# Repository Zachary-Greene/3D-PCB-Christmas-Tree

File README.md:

# 3D-PCB-Christmas-Tree
This is a repository for my 3D free standing PCB christmas tree project. It is two PCB's that slide together to create a free standing decoration. To secure the PCB's together, you solder them together using the exposed pads that ideally will line up. Included within the repository is a copy of this readme file, a license file and the eagle files.

## Parts and Assembly
### Assembly
Solder the smallest components on the boards first otherwise it'll be harder if you solder the bigger parts first. Then solder the larger components such as the battery holder. Afterwards, solder the two boards together with a strong connection, to prevent the solder from dripping down the board, put them on their sides so that they form a 'V' shape then solder.

### Parts
* ATtiny85 SOP Package Digikey ATTINY85-20SURCT-ND x1
* CR2032 Coin Cell Holder Core Electronics/Sparkfun PRT-00783 x1
* CR2032 Coin Cell x1
* APA102C-5050 RGB LED Core Electronics/Sparkfun COM-16345 x11
* 0603 (Metric) 1K Ohm Resistor Digikey 311-1KMCT-ND x1

## License
See LICENSE.md

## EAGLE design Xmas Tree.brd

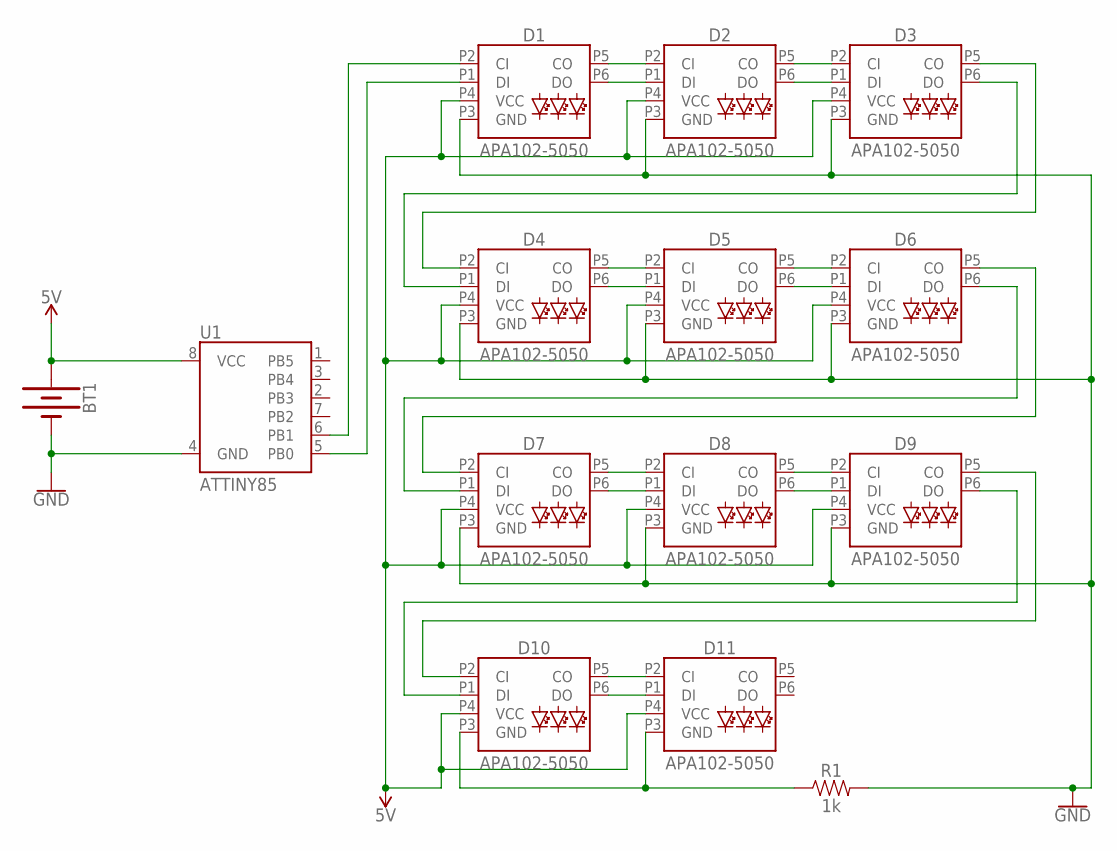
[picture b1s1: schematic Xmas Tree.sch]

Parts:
BT1: BATTERY-20MM_PTH; BATTCOM_20MM_PTH
D1, D2, D3, D4, D5, D6, D7, D8, D9, D10, D11: APA102-5050
R1: 1k; 0603
U1: ATTINY85

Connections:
5V: BT1.1 (+), D1.P4 (VCC), D2.P4 (VCC), D3.P4 (VCC), D4.P4 (VCC), D5.P4 (VCC), D6.P4 (VCC), D7.P4 (VCC), D8.P4 (VCC), D9.P4 (VCC), D10.P4 (VCC), D11.P4 (VCC), U1.8 (VCC)
CI1: D1.P2 (CI), U1.6 (PB1)
CI2: D1.P5 (CO), D2.P2 (CI)
CI3: D2.P5 (CO), D3.P2 (CI)
CI4: D3.P5 (CO), D4.P2 (CI)
CI5: D4.P5 (CO), D5.P2 (CI)
CI6: D5.P5 (CO), D6.P2 (CI)
CI7: D6.P5 (CO), D7.P2 (CI)
CI8: D7.P5 (CO), D8.P2 (CI)
CI9: D8.P5 (CO), D9.P2 (CI)
CI10: D9.P5 (CO), D10.P2 (CI)
CI11: D10.P5 (CO), D11.P2 (CI)
DI1: D1.P1 (DI), U1.5 (PB0)
DI2: D1.P6 (DO), D2.P1 (DI)
DI3: D2.P6 (DO), D3.P1 (DI)
DI4: D3.P6 (DO), D4.P1 (DI)
DI5: D4.P6 (DO), D5.P1 (DI)
DI6: D5.P6 (DO), D6.P1 (DI)
DI7: D6.P6 (DO), D7.P1 (DI)
DI8: D7.P6 (DO), D8.P1 (DI)
DI9: D8.P6 (DO), D9.P1 (DI)
DI10: D9.P6 (DO), D10.P1 (DI)
DI11: D10.P6 (DO), D11.P1 (DI)
GND: BT1.2 (-), D1.P3 (GND), D2.P3 (GND), D3.P3 (GND), D4.P3 (GND), D5.P3 (GND), D6.P3 (GND), D7.P3 (GND), D8.P3 (GND), D9.P3 (GND), D10.P3 (GND), D11.P3 (GND), R1.1, R1.2, U1.4 (GND)

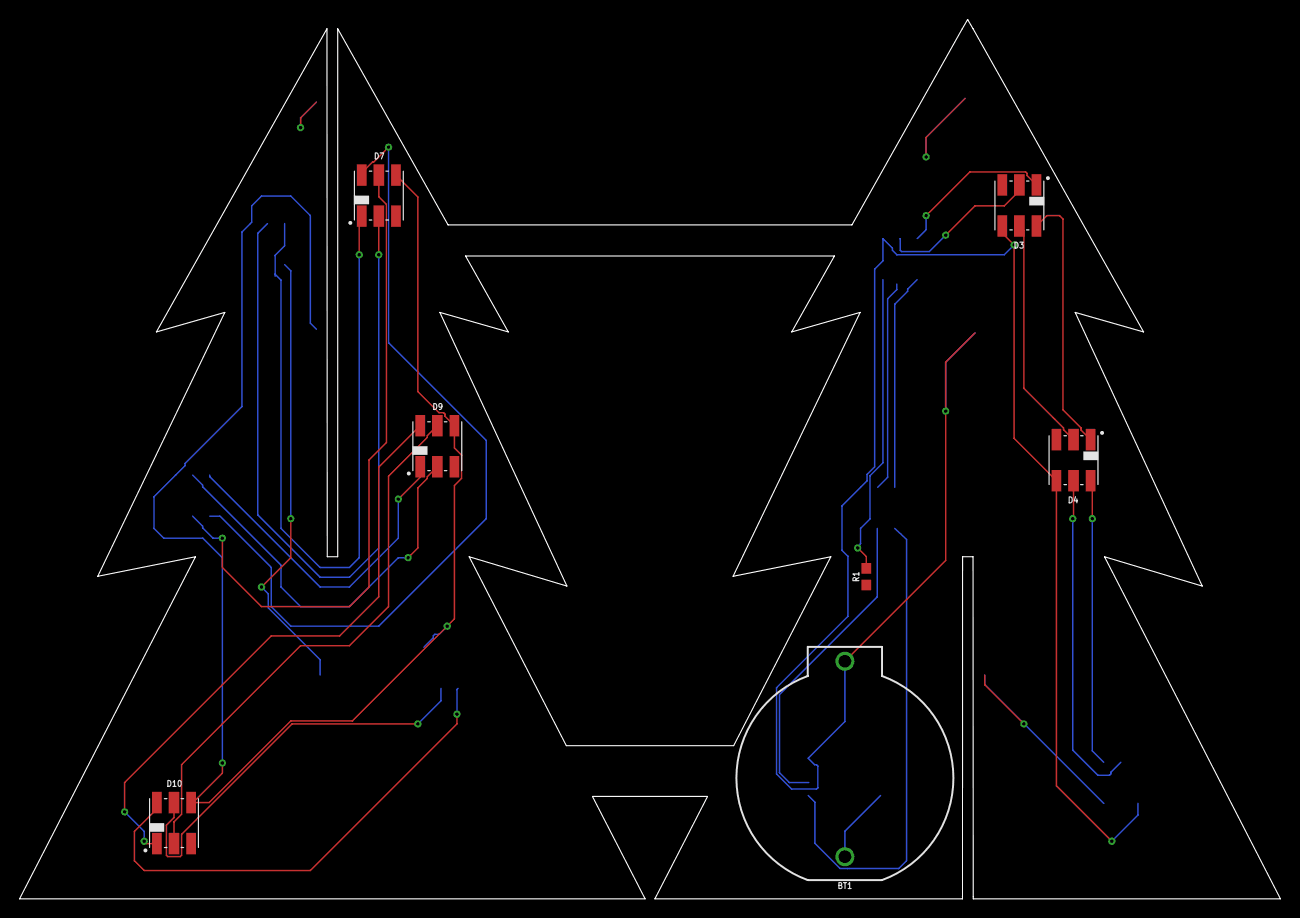
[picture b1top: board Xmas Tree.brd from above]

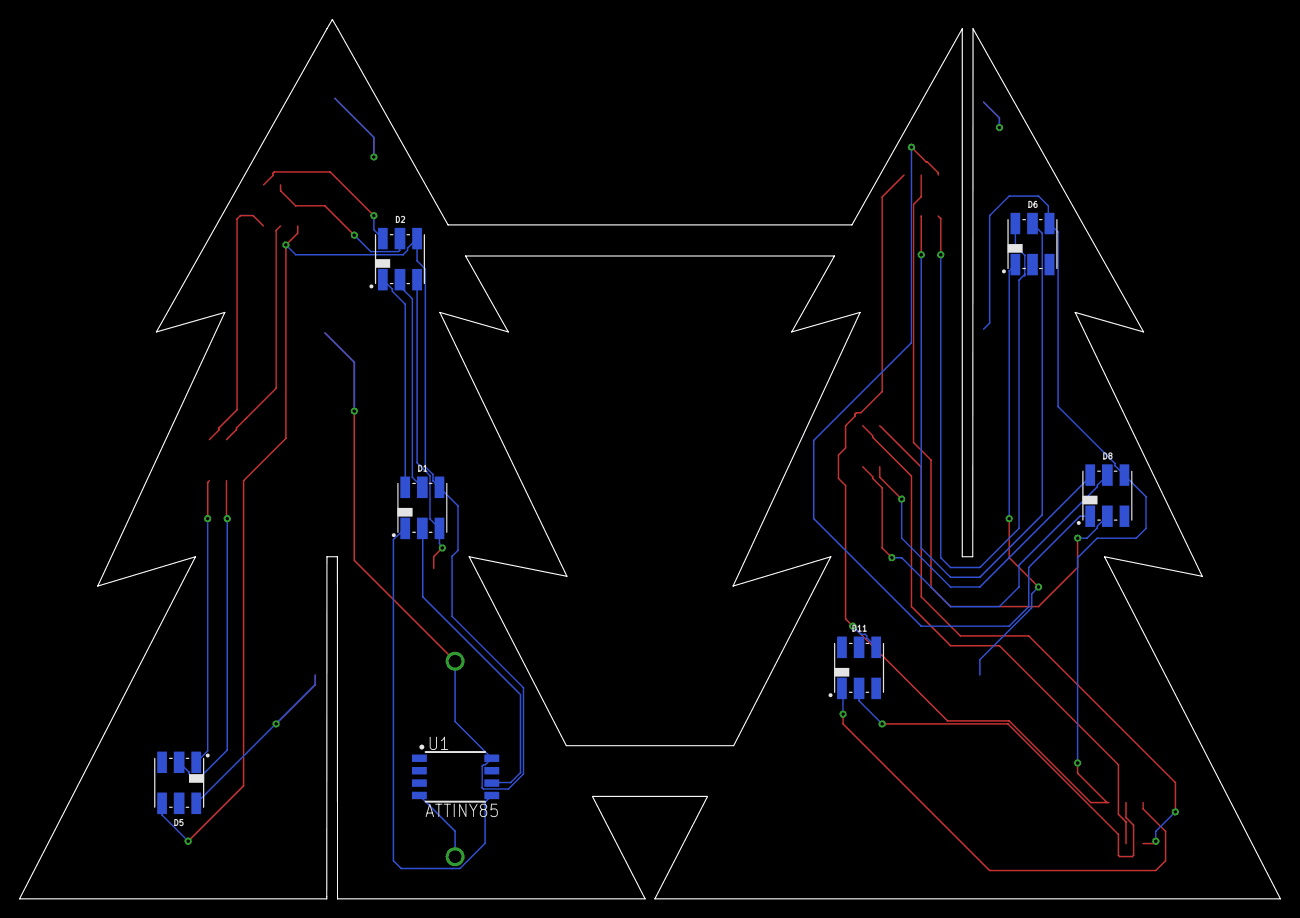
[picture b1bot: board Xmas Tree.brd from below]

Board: 2 copper layers, 129.0 x 90.0 mm, 14 parts (7 on the bottom side), 24 nets.

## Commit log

2020-10-28 Add files via upload
    V1 Added the schematic and board files

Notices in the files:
parts and their libraries:
SparkFun-LED: Licensing: Creative Commons ShareAlike 4.0 International - https://creativecommons.org/licenses/by-sa/4.0
